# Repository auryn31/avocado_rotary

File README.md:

# Avocado Keyboard

The Avocado keyboard is a 34-key split, columnar, ergonomic keyboard. It is designed to be a comfortable and efficient keyboard for everyday use.

[YouTube Video](https://youtu.be/2LzUSILI9gA)

## Features

- **Split, Columnar Layout:** The split design allows you to position the two halves of the keyboard to match your shoulder width, promoting a more natural and comfortable typing posture. The columnar layout aligns the keys with the natural movement of your fingers.
- **34-Key Layout:** The 34-key layout is a compact layout that is designed to be efficient and easy to learn. It uses layers to provide access to all of the keys that you need.
- **Hotswap Sockets:** Hotswap sockets allow you to easily change your switches without soldering. This makes it easy to try out new switches and to find the ones that you like best.
- **Rotary Encoder:** The rotary encoder can be used for a variety of functions, such as scrolling, volume control, and undo/redo.
- **Wireless:** The Avocado keyboard is a wireless keyboard that uses the Seeed Studio XIAO BLE controller.
- **ZMK Firmware:** The Avocado keyboard uses the ZMK firmware, which is a powerful and flexible open-source keyboard firmware.

## Hardware

### PCB

The PCB is designed with Ergogen and KiCad. The design files are located in the `ergogen` and `kicad` directories.

- **MCU:** Seeed Studio XIAO BLE
- **Switches:** Choc v1
- **Diodes:** SOD-123W

### Case

The case is a 3D printed case. The design files are not yet available.

### Bill of Materials (BOM)

| Component             | Quantity | Notes               |
| --------------------- | -------- | ------------------- |
| Seeed Studio XIAO BLE | 2        |                     |
| Choc v1 Switches      | 34       |                     |
| SOD-123W Diodes       | 34       |                     |
| Hotswap Sockets       | 34       |                     |
| Rotary Encoder        | 1        | EC11 or EC12        |
| Battery               | 2        | 301230 LiPo battery |
| On/Off Switch         | 2        |                     |
| Reset Switch          | 2        |                     |
| M2 Screws             | 12       | For the case        |
| Keycaps               | 34       |                     |

## Firmware

The Avocado keyboard uses the ZMK firmware. The firmware is located in the `config` directory.

### Building and Flashing

The firmware is built automatically by GitHub Actions. You can download the latest firmware from the [Actions] tab on the GitHub repository.

To flash the firmware, you will need to put your XIAO BLE into bootloader mode. To do this, connect the XIAO BLE to your computer and double-press the reset button. The XIAO BLE will then show up as a USB mass storage device. You can then drag and drop the firmware file onto the XIAO BLE.

## Build Guide

A detailed build guide is not yet available. However, the build process is similar to other custom keyboards. You will need to solder the diodes, hotswap sockets, and other components to the PCB. You will then need to assemble the case and install the keycaps.

## Local Development

### Ergogen

#### Build

This will run Ergogen and build all of the output files.

```bash
npm run ergogen:build
```

#### Watch

This will watch the `config.yaml` file and the `footprints` directory and run the build command whenever there are changes.

```bash
npm run ergogen:watch
```

### ZMK

```sh
# One time setup
git clone https://github.com/zmkfirmware/zmk.git
npm install -g @devcontainers/cli

docker volume create --driver local -o o=bind -o type=none \
  -o device="/Users/auryn/coding/avocado/config" zmk-config
docker volume create --driver local -o o=bind -o type=none \
  -o device="/Users/auryn/coding/avocado/zephyr" zmk-modules
devcontainer up --workspace-folder "/Users/auryn/coding/zmk"

docker exec -w /workspaces/zmk -it a29e880249f3 /bin/bash

cd app
west update
west config build.cmake-args -- "-DSHIELD=avocado_left -DZMK_CONFIG=/workspaces/zmk-config"
west config build.cmake-args -- "-DSHIELD=avocado_right -DZMK_CONFIG=/workspaces/zmk-config"

# One or the other
west build -p -b nice_nano_v2 -- -DSHIELD=avocado_left
# west build -p -b seeeduino_xiao_ble -- -DSHIELD=avocado_left
```

## Acknowledgements

- [Ergogen](https://github.com/ergogen/ergogen)
- [Absolem Club Discord](https://discord.gg/nbKcAZB)
- [V4 Migration Guide](https://github.com/tsteffek/Ergogen-V4-Migration-Guide)
- [Claw](https://gitlab.com/Audijo/keyboard)
- [MrKeyboard](https://github.com/MrCarney/mrkeyboard)
- [Corne keyboard](https://github.com/foostan/crkbd)
- [ZMK](https://github.com/zmkfirmware/zmk)
- [Miryoku ZMK](https://github.com/manna-harbour/miryoku_zmk)

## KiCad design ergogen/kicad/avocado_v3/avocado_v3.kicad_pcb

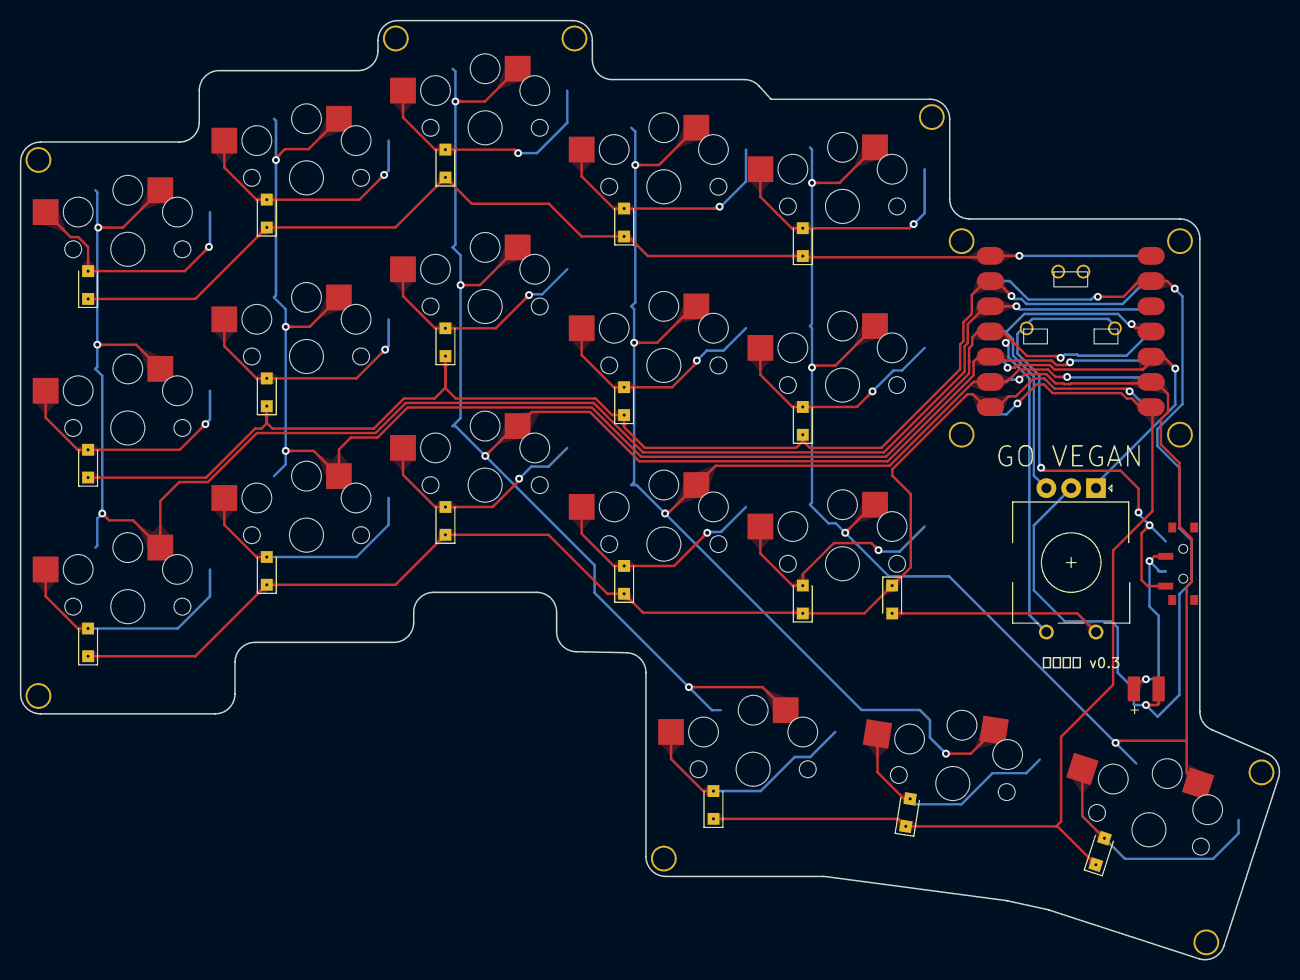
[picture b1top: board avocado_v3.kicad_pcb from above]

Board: 2 copper layers, 126.8 x 94.6 mm, 53 parts (0 on the bottom side), 14 nets.

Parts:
D1, D2, D3, D4, D5, D6, D7, D8, D9, D10, D11, D12, D13, D14, D15, D16, D17, D18, D19: Nexperia_CFP3_SOD-123W
H1, H2, H3, H4, H5, H6, H7, H8, H9, H10, H11, H12: mounting_hole
MCU1: xiao-ble-smd-reversible
PAD1: pads
S1, S2, S3, S4, S5, S6, S7, S8, S9, S10, S11, S12, S13, S14, S15, S16, S17, S18: PG1350
T1: SW_SPDT_PCM12
_1: rotary_encoder

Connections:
B+: PAD1.1, PAD1.2, T1.2
D0: D3.1, D3.2, D6.1, D6.2, D9.1, D9.2, D12.1, D12.2, D15.1, D15.2, MCU1.1, S3.2, S6.2, S9.2, S12.2, S15.2
D1: D2.1, D2.2, D5.1, D5.2, D8.1, D8.2, D11.1, D11.2, D14.1, D14.2, MCU1.2, S2.2, S5.2, S8.2, S11.2, S14.2
D2: MCU1.3, S1.1, S2.1, S3.1
D3: MCU1.4, S4.1, S5.1, S6.1, _1.2
D4: MCU1.5, S7.1, S8.1, S9.1, S16.1
D5: MCU1.6, S10.1, S11.1, S12.1, S17.1
D6: D1.1, D1.2, D4.1, D4.2, D7.1, D7.2, D10.1, D10.2, D13.1, D13.2, D19.1, D19.2, MCU1.7, S1.2, S4.2, S7.2, S10.2, S13.2, _1.1
D7: D16.1, D16.2, D17.1, D17.2, D18.1, D18.2, MCU1.8, S16.2, S17.2, S18.2
D8: MCU1.9, S13.1, S14.1, S15.1, S18.1
D9: MCU1.10, _1.A
D10: MCU1.11, _1.B
GND: MCU1.13, MCU1.17, PAD1.1, PAD1.2, _1.C
pos: MCU1.19, T1.1

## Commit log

2025-09-21 update config
2025-09-21 update steps and config
2025-09-21 fix rotary encoder net
2025-09-21 different syntax
2025-09-21 non minimal logs
2025-09-21 get full log
2025-09-21 update to enabled
2025-09-21 add reset
2025-09-21 try enable ec11
2025-09-21 remove broken config
2025-09-21 add correct config
2025-09-21 update steps
2025-09-21 update rotation
2025-09-22 update right encoder
2025-09-25 update pcb (not finished)
